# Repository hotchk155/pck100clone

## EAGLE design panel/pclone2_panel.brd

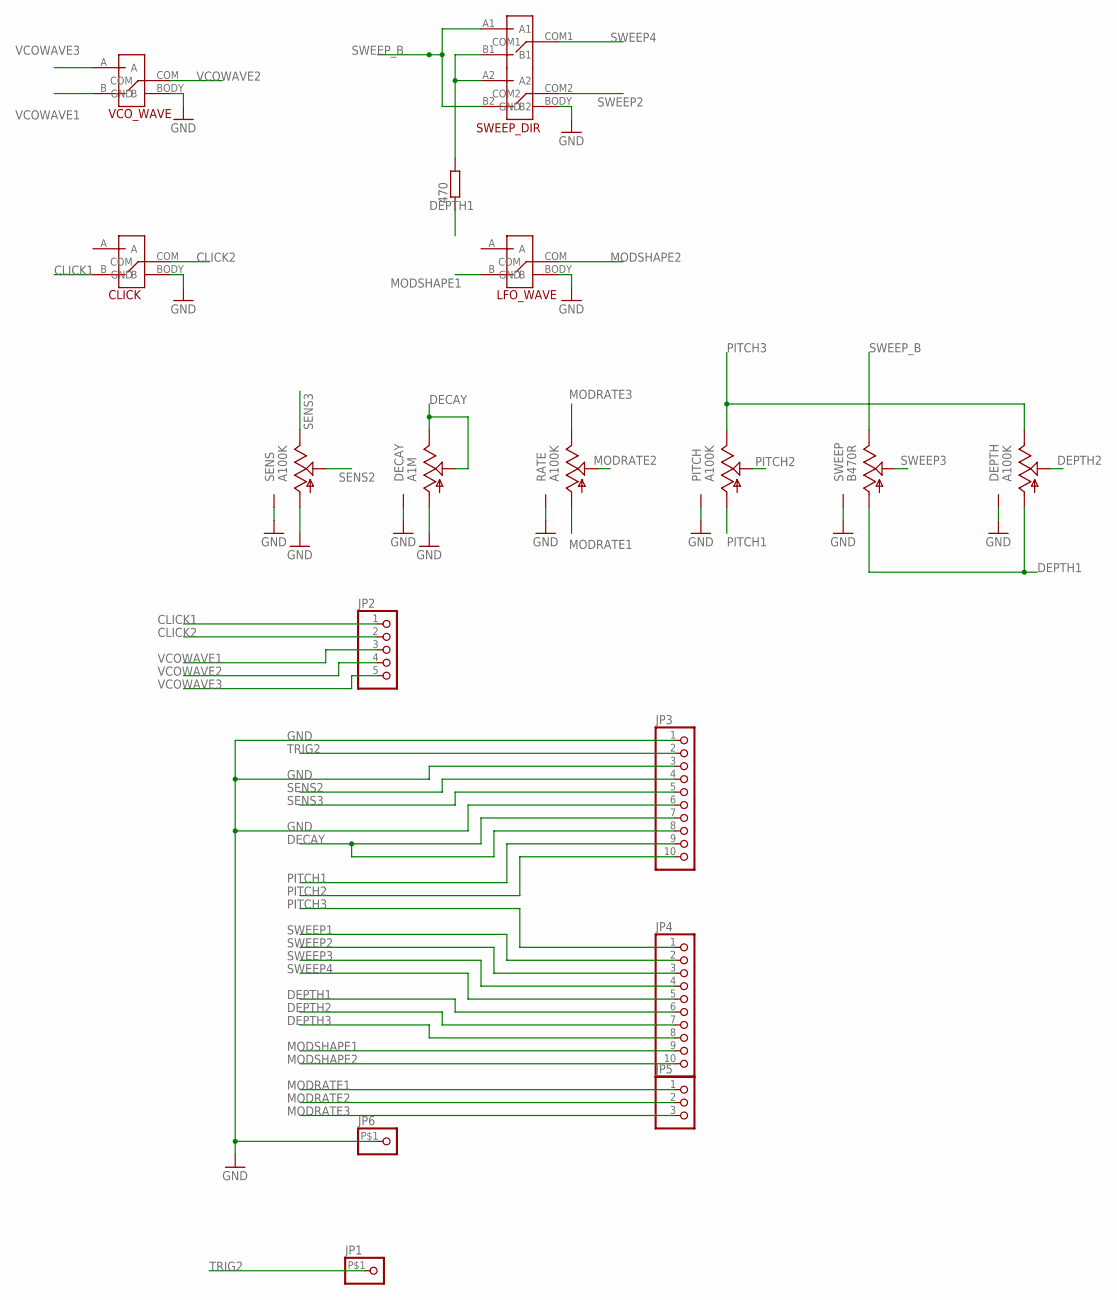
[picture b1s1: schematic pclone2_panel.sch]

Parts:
470: R-EU_R0805; R0805
CLICK: SPD_SMTD; SPDT_SMTD
DECAY: A1M; 16MM_POT_SMTD
DEPTH: A100K; 16MM_POT_SMTD
JP1, JP6: PINHD-1X1SMT; PINHEADPAD
JP2: HEADER-1X5SMT; 1X05_SMT
JP3, JP4: HEADER-1X10SMT; 1X10_SMT
JP5: HEADER-1X3SMT; 1X03_SMT
LFO_WAVE: SPD_SMTD; SPDT_SMTD
PITCH: A100K; 16MM_POT_SMTD
RATE: A100K; 16MM_POT_SMTD
SENS: A100K; 16MM_POT_SMTD
SWEEP: B470R; 16MM_POT_SMTD
SWEEP_DIR: DPDT_SMTD
VCO_WAVE: SPD_SMTD; SPDT_SMTD

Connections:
CLICK1: CLICK.B, JP2.1
CLICK2: CLICK.COM, JP2.2
DECAY: DECAY.B, DECAY.W, JP3.7, JP3.8
DEPTH1: 470.1, DEPTH.A, JP4.6, SWEEP.A
DEPTH2: DEPTH.W, JP4.7
DEPTH3: JP4.8
GND: CLICK.BODY (GND), DECAY.A, DECAY.BODY (GND), DEPTH.BODY (GND), JP3.1, JP3.3, JP3.6, JP6.P$1, LFO_WAVE.BODY (GND), PITCH.BODY (GND), RATE.BODY (GND), SENS.A, SENS.BODY (GND), SWEEP.BODY (GND), SWEEP_DIR.BODY (GND), VCO_WAVE.BODY (GND)
MODRATE1: JP5.1, RATE.A
MODRATE2: JP5.2, RATE.W
MODRATE3: JP5.3, RATE.B
MODSHAPE1: JP4.9, LFO_WAVE.B
MODSHAPE2: JP4.10, LFO_WAVE.COM
unnamed: 470.2, SWEEP_DIR.A2, SWEEP_DIR.B1
PITCH1: JP3.9, PITCH.A
PITCH2: JP3.10, PITCH.W
PITCH3: DEPTH.B, JP4.1, PITCH.B
SENS2: JP3.4, SENS.W
SENS3: JP3.5, SENS.B
SWEEP1: JP4.2
SWEEP2: JP4.3, SWEEP_DIR.COM2
SWEEP3: JP4.4, SWEEP.W
SWEEP4: JP4.5, SWEEP_DIR.COM1
SWEEP_B: SWEEP.B, SWEEP_DIR.A1, SWEEP_DIR.B2
TRIG2: JP1.P$1, JP3.2
VCOWAVE1: JP2.3, VCO_WAVE.B
VCOWAVE2: JP2.4, VCO_WAVE.COM
VCOWAVE3: JP2.5, VCO_WAVE.A

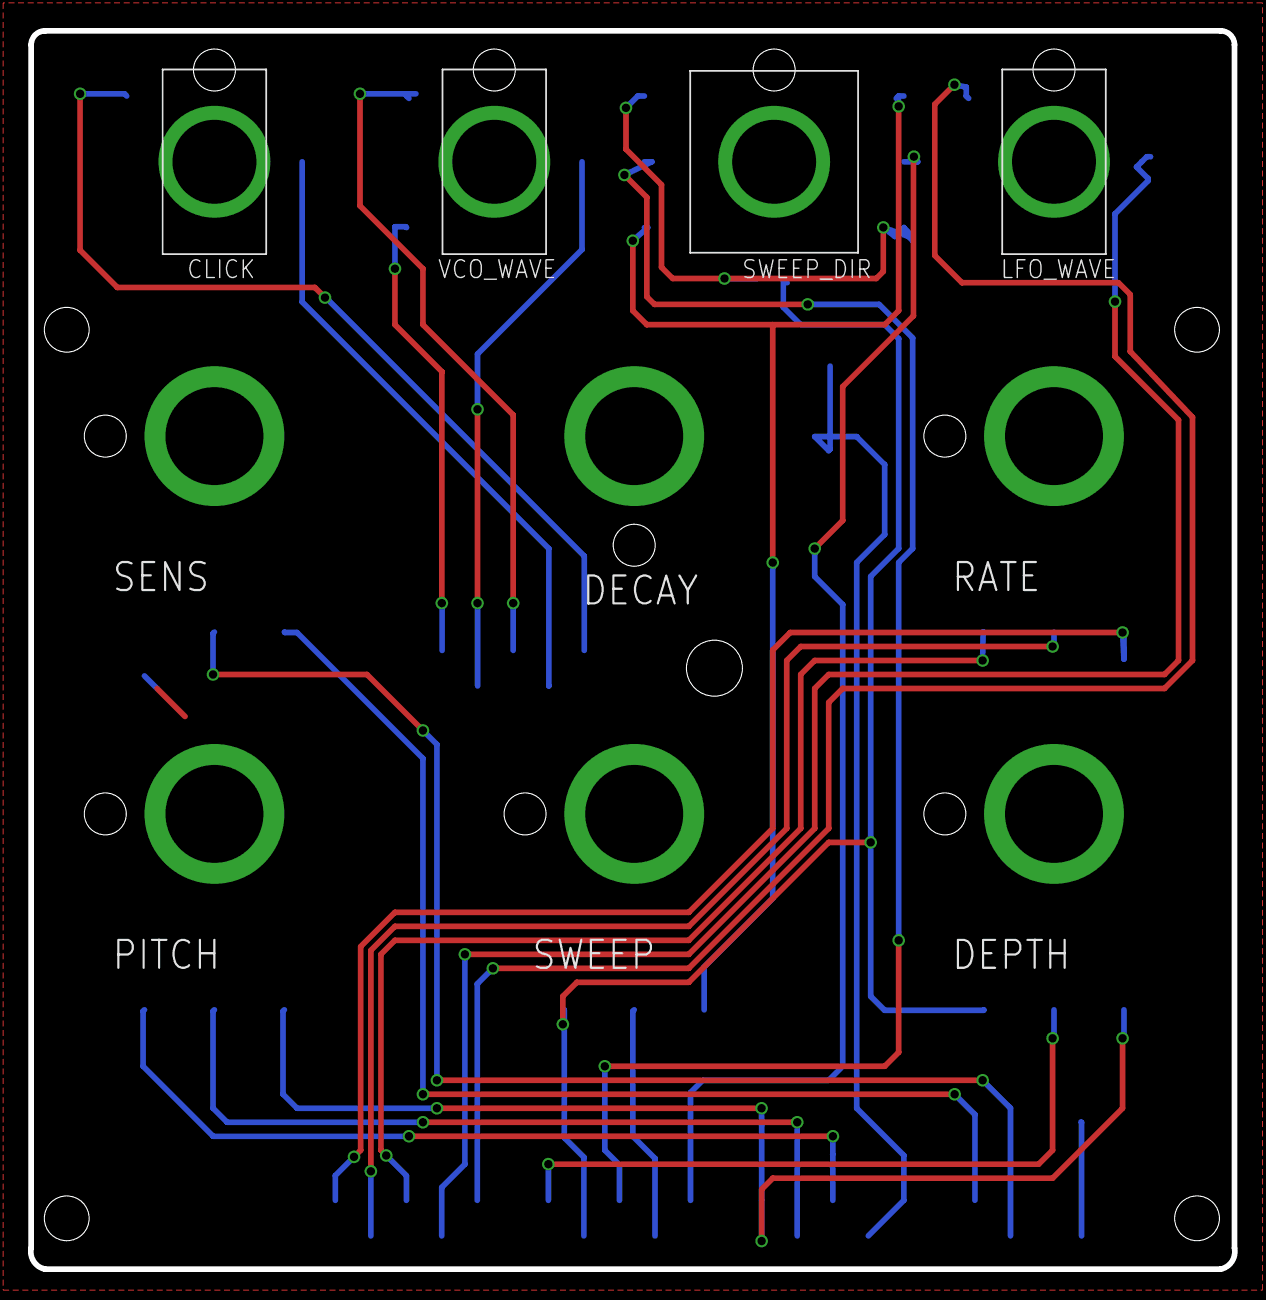
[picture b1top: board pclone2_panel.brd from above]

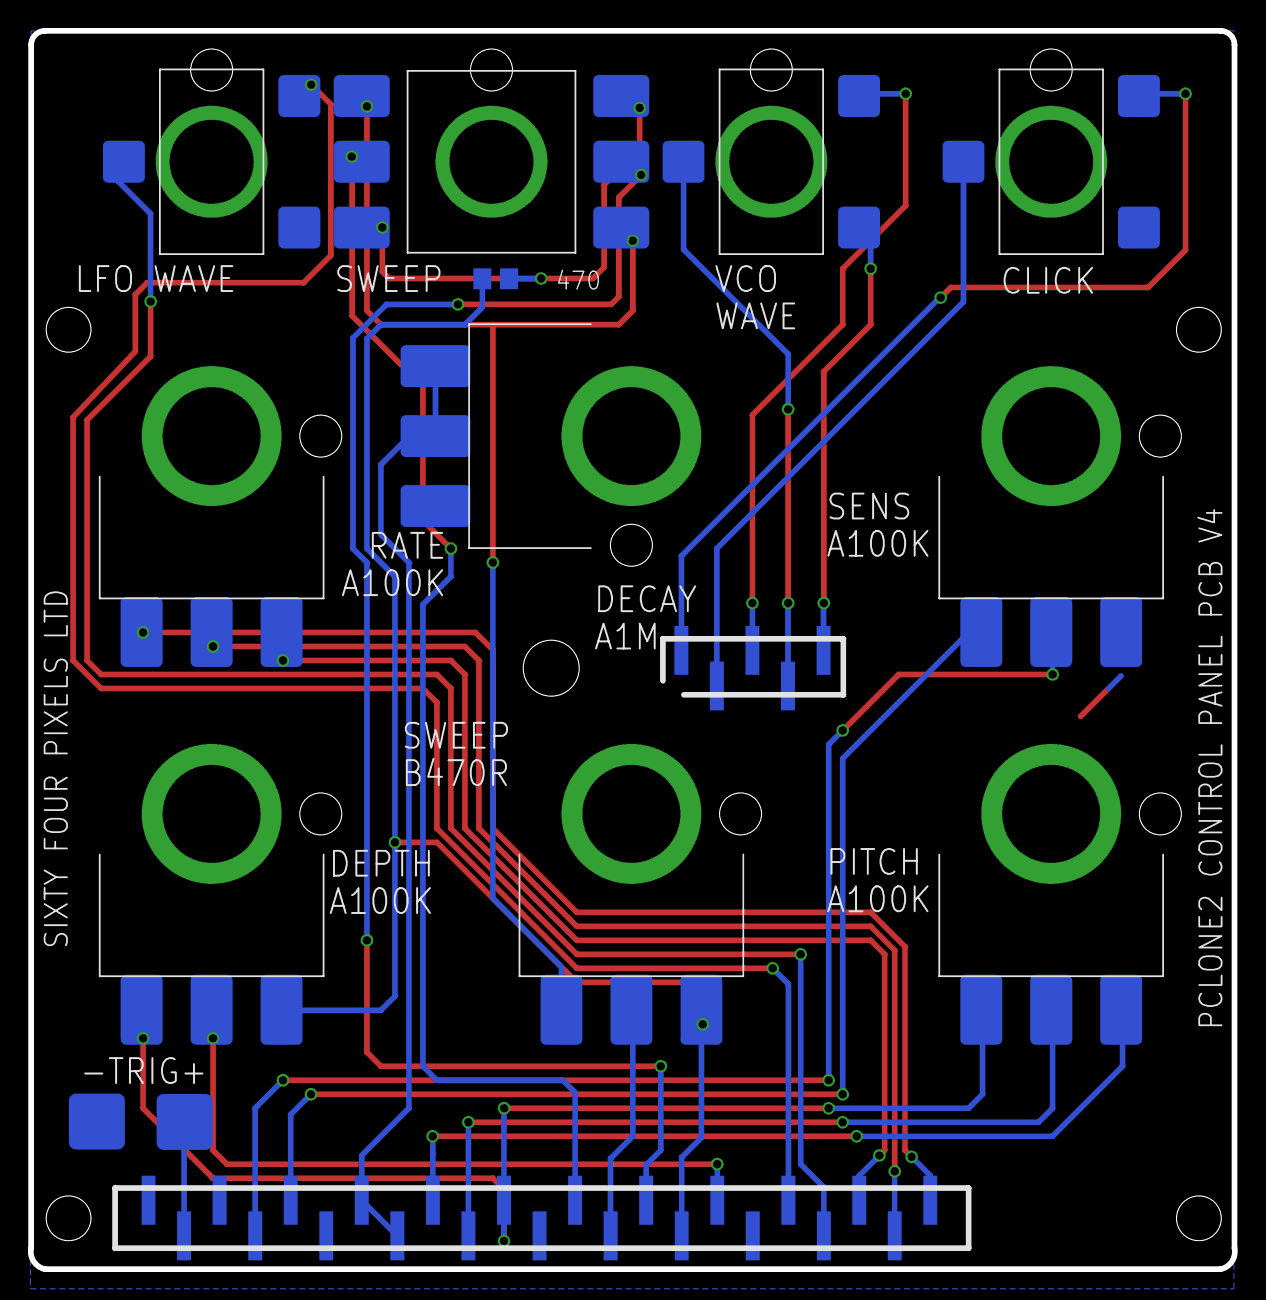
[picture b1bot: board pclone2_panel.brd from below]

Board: 2 copper layers, 86.0 x 88.5 mm, 17 parts (7 on the bottom side), 25 nets.

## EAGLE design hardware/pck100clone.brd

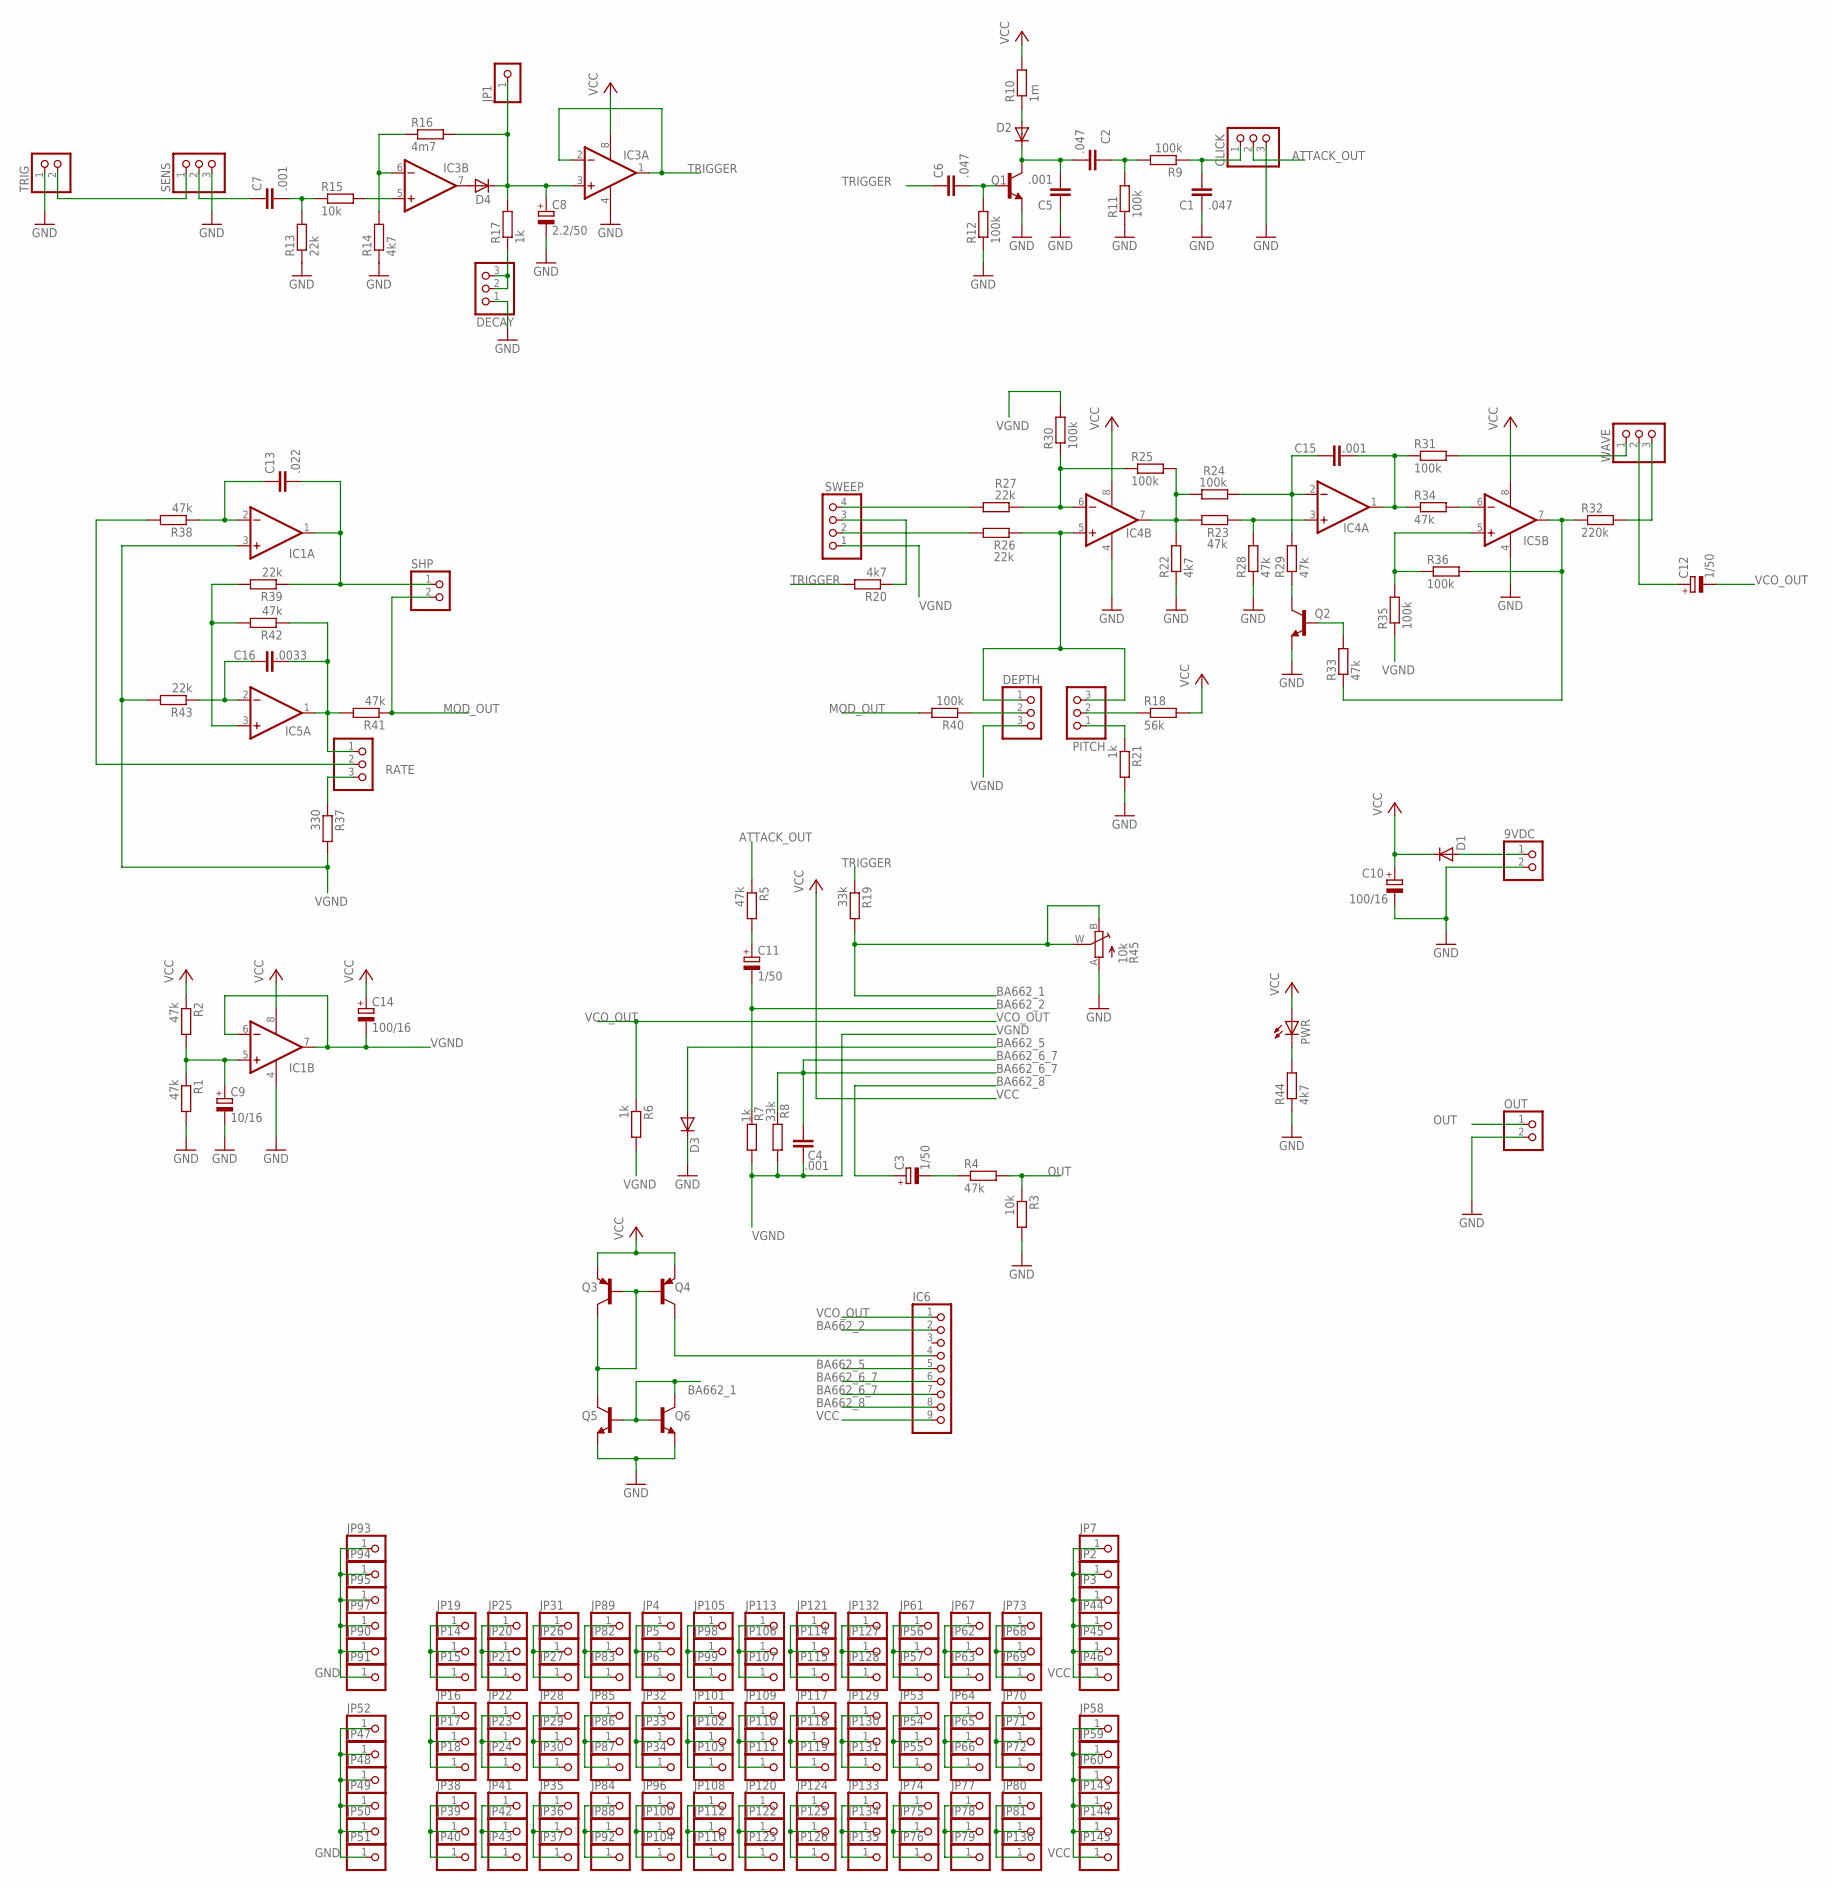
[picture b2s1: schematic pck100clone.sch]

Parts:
9VDC: PINHD-1X2; 1X02
C1, C2, C6: .047; C050-025X075
C3, C11, C12: 1/50; E2,5-5
C4, C5, C7, C15: .001; C050-025X075
C8: 2.2/50; E2,5-5
C9: 10/16; E2,5-5
C10, C14: 100/16; E2,5-5
C13: .022; C050-025X075
C16: .0033; C050-025X075
CLICK: PINHD-1X3; 1X03
D1: 1N4004; DO41-10
D2, D3, D4: 1N4148DO35-7; DO35-7
DECAY: PINHD-1X3; 1X03
DEPTH: PINHD-1X3; 1X03
IC1, IC3, IC4, IC5: LM358N; DIL08
IC6: PINHD-1X9; 1X09
JP1, JP2, JP3, JP4, JP5, JP6, JP7, JP14, JP15, JP16, JP17, JP18, JP19, JP20, JP21, JP22, JP23, JP24, JP25, JP26, JP27, JP28, JP29, JP30, JP31, JP32, JP33, JP34, JP35, JP36, JP37, JP38, JP39, JP40, JP41, JP42, JP43, JP44, JP45, JP46, JP47, JP48, JP49, JP50, JP51, JP52, JP53, JP54, JP55, JP56, JP57, JP58, JP59, JP60, JP61, JP62, JP63, JP64, JP65, JP66, JP67, JP68, JP69, JP70, JP71, JP72, JP73, JP74, JP75, JP76, JP77, JP78, JP79, JP80, JP81, JP82, JP83, JP84, JP85, JP86, JP87, JP88, JP89, JP90, JP91, JP92, JP93, JP94, JP95, JP96, JP97, JP98, JP99, JP100, JP101, JP102, JP103, JP104, JP105, JP106, JP107, JP108, JP109, JP110, JP111, JP112, JP113, JP114, JP115, JP116, JP117, JP118, JP119, JP120, JP121, JP122, JP123, JP124, JP125, JP126, JP127, JP128, JP129, JP130, JP131, JP132, JP133, JP134, JP135, JP136, JP143, JP144, JP145: PINHD-1X1; 1X01
OUT: PINHD-1X2; 1X02
PITCH: PINHD-1X3; 1X03
PWR: LED3MM
Q1, Q2: 2SC945; TO92-ECB
Q3, Q4: 2N3906; TO92
Q5, Q6: 2N3904; TO92
R1, R2, R4, R5, R23, R28, R29, R33, R34, R38, R41, R42: 47k; 0207/7
R3, R15: 10k; 0207/7
R6, R7, R17, R21: 1k; 0207/7
R8, R19: 33k; 0207/7
R9, R11, R12, R24, R25, R30, R31, R35, R36, R40: 100k; 0207/7
R10: 1m; 0207/7
R13, R26, R27, R39, R43: 22k; 0207/7
R14, R20, R22, R44: 4k7; 0207/7
R16: 4m7; 0207/7
R18: 56k; 0207/7
R32: 220k; 0207/7
R37: 330; 0207/7
R45: 10k; TRIM-N
RATE: PINHD-1X3; 1X03
SENS: PINHD-1X3; 1X03
SHP: PINHD-1X2; 1X02
SWEEP: PINHD-1X4; 1X04
TRIG: PINHD-1X2; 1X02
WAVE: PINHD-1X3; 1X03

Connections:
ATTACK_OUT: CLICK.2, R5.1
BA662_1: Q5.2 (B), Q6.1 (C), Q6.2 (B), R19.2, R45.B (E), R45.W (S)
BA662_2: C11.-, IC6.2, R7.1
BA662_5: D3.A, IC6.5
BA662_6_7: C4.2, IC6.6, IC6.7, R8.1
BA662_8: C3.+, IC6.8
GND: 9VDC.2, C1.1, C5.1, C8.-, C9.-, C10.-, CLICK.3, D3.C, DECAY.1, IC1.4 (V-), IC3.4 (V-), IC4.4 (V-), IC5.4 (V-), JP47.1, JP48.1, JP49.1, JP50.1, JP51.1, JP52.1, JP90.1, JP91.1, JP93.1, JP94.1, JP95.1, JP97.1, OUT.2, Q1.E, Q2.E, Q5.3 (E), Q6.3 (E), R1.2, R3.2, R11.1, R12.1, R13.1, R14.1, R21.2, R22.1, R28.1, R44.1, R45.A, SENS.3, TRIG.1
MOD_OUT: R40.2, R41.1, SHP.2
unnamed: SENS.1, TRIG.2
unnamed: 9VDC.1, D1.A
unnamed: C7.1, SENS.2
unnamed: C7.2, R13.2, R15.1
unnamed: IC3.5 (+IN), R15.2
unnamed: IC3.6 (-IN), R14.2, R16.1
unnamed: D4.A, IC3.7 (OUT)
unnamed: C8.+, D4.C, IC3.3 (+IN), JP1.1, R16.2, R17.2
unnamed: DECAY.2, DECAY.3, R17.1
unnamed: C6.2, Q1.B, R12.2
unnamed: C2.2, C5.2, D2.C, Q1.C
unnamed: D2.A, R10.1
unnamed: C2.1, R9.2, R11.2
unnamed: C1.2, CLICK.1, R9.1
unnamed: C13.2, IC1.1 (OUT), R39.1, SHP.1
unnamed: C13.1, IC1.2 (-IN), R38.1
unnamed: R38.2, RATE.2
unnamed: JP4.1, JP5.1, JP6.1
unnamed: C16.1, IC5.2 (-IN), R43.1
unnamed: C16.2, IC5.1 (OUT), R41.2, R42.1, RATE.1
unnamed: R20.1, SWEEP.3
unnamed: R37.1, RATE.3
unnamed: IC5.3 (+IN), R39.2, R42.2
unnamed: R27.2, SWEEP.4
unnamed: R26.2, SWEEP.2
unnamed: IC4.6 (-IN), R25.1, R27.1, R30.1
unnamed: DEPTH.1, IC4.5 (+IN), PITCH.3, R26.1
unnamed: DEPTH.2, R40.1
unnamed: PITCH.2, R18.1
unnamed: PITCH.1, R21.1
unnamed: C9.+, IC1.5 (+IN), R1.1, R2.2
unnamed: IC4.7 (OUT), R22.2, R23.1, R24.1, R25.2
unnamed: IC4.3 (+IN), R23.2, R28.2
unnamed: C15.2, IC4.2 (-IN), R24.2, R29.2
unnamed: Q2.C, R29.1
unnamed: Q2.B, R33.2
unnamed: C15.1, IC4.1 (OUT), R31.1, R34.1
unnamed: IC5.6 (-IN), R34.2
unnamed: R31.2, WAVE.1
unnamed: IC5.7 (OUT), R32.1, R33.1, R36.2
unnamed: R32.2, WAVE.3
unnamed: IC5.5 (+IN), R35.2, R36.1
unnamed: C12.+, WAVE.2
unnamed: PWR.K (C), R44.2
unnamed: IC6.4, Q4.1 (C)
unnamed: C11.+, R5.2
unnamed: Q3.1 (C), Q3.2 (B), Q4.2 (B), Q5.1 (C)
unnamed: JP14.1, JP15.1, JP19.1
unnamed: C3.-, R4.1
unnamed: JP16.1, JP17.1, JP18.1
unnamed: JP20.1, JP21.1, JP25.1
unnamed: JP22.1, JP23.1, JP24.1
unnamed: JP26.1, JP27.1, JP31.1
unnamed: JP28.1, JP29.1, JP30.1
unnamed: JP32.1, JP33.1, JP34.1
unnamed: JP35.1, JP36.1, JP37.1
unnamed: JP38.1, JP39.1, JP40.1
unnamed: JP41.1, JP42.1, JP43.1
unnamed: JP53.1, JP54.1, JP55.1
unnamed: JP56.1, JP57.1, JP61.1
unnamed: JP62.1, JP63.1, JP67.1
unnamed: JP64.1, JP65.1, JP66.1
unnamed: JP68.1, JP69.1, JP73.1
unnamed: JP70.1, JP71.1, JP72.1
unnamed: JP74.1, JP75.1, JP76.1
unnamed: JP77.1, JP78.1, JP79.1
unnamed: JP80.1, JP81.1, JP136.1
unnamed: JP98.1, JP99.1, JP105.1
unnamed: JP82.1, JP83.1, JP89.1
unnamed: JP85.1, JP86.1, JP87.1
unnamed: JP101.1, JP102.1, JP103.1
unnamed: JP106.1, JP107.1, JP113.1
unnamed: JP109.1, JP110.1, JP111.1
unnamed: JP114.1, JP115.1, JP121.1
unnamed: JP117.1, JP118.1, JP119.1
unnamed: JP84.1, JP88.1, JP92.1
unnamed: JP96.1, JP100.1, JP104.1
unnamed: JP108.1, JP112.1, JP116.1
unnamed: JP120.1, JP122.1, JP123.1
unnamed: JP124.1, JP125.1, JP126.1
unnamed: JP127.1, JP128.1, JP132.1
unnamed: JP129.1, JP130.1, JP131.1
unnamed: JP133.1, JP134.1, JP135.1
OUT: OUT.1, R3.1, R4.2
TRIGGER: C6.1, IC3.1 (OUT), IC3.2 (-IN), R19.1, R20.2
VCC: C10.+, C14.+, D1.C, IC1.8 (V+), IC3.8 (V+), IC4.8 (V+), IC5.8 (V+), IC6.9, JP2.1, JP3.1, JP7.1, JP44.1, JP45.1, JP46.1, JP58.1, JP59.1, JP60.1, JP143.1, JP144.1, JP145.1, PWR.A, Q3.3 (E), Q4.3 (E), R2.1, R10.2, R18.2
VCO_OUT: C12.-, IC6.1, R6.1
VGND: C4.1, C14.-, DEPTH.3, IC1.3 (+IN), IC1.6 (-IN), IC1.7 (OUT), R6.2, R7.2, R8.2, R30.2, R35.1, R37.2, R43.2, SWEEP.1

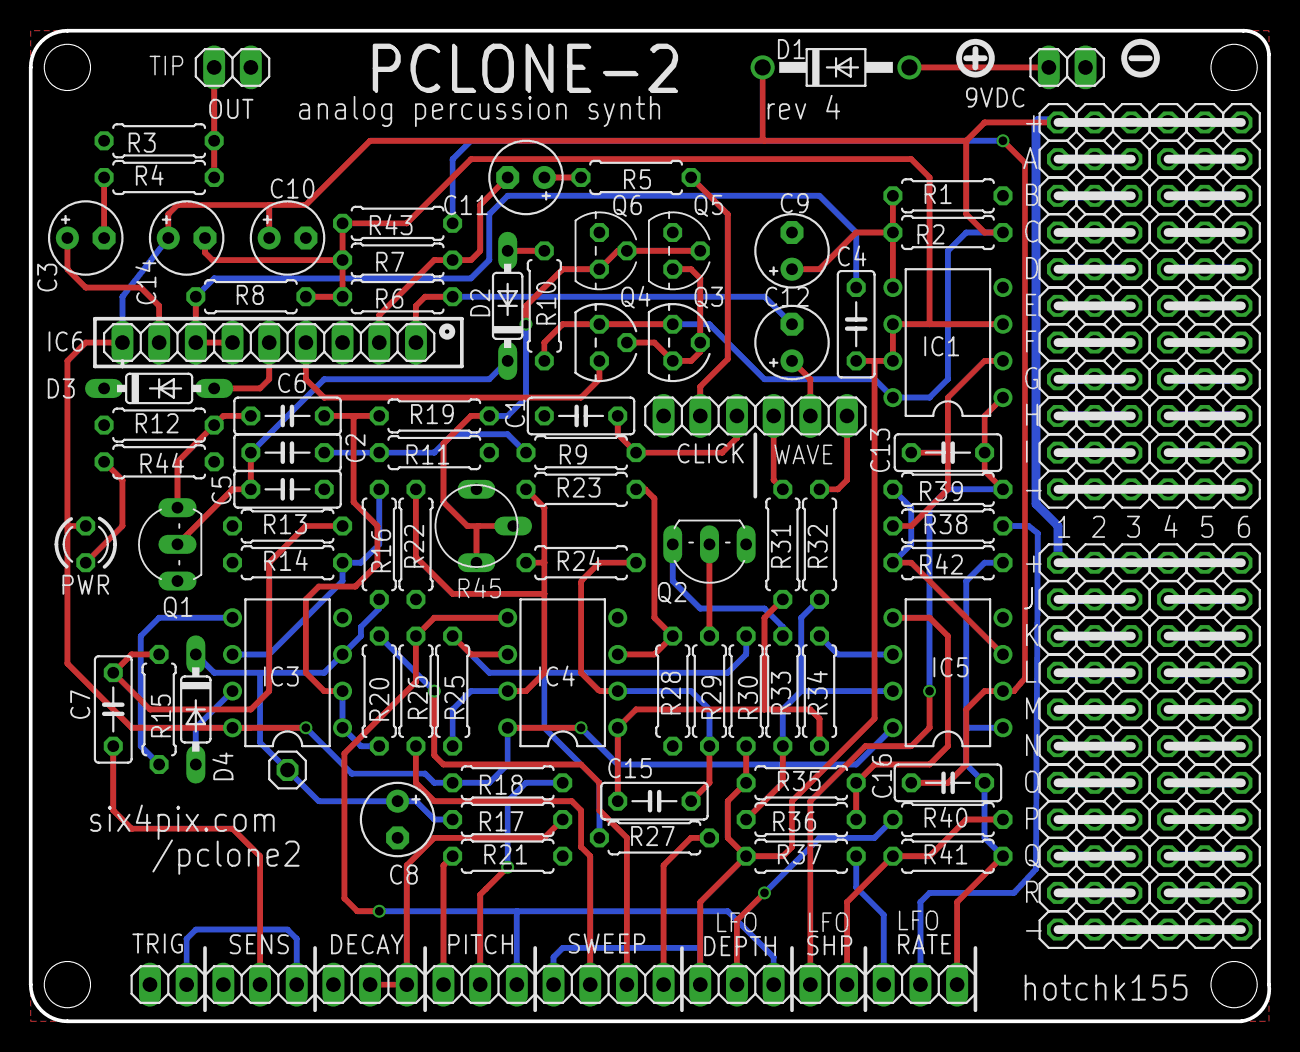
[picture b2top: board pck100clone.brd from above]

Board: 2 copper layers, 85.7 x 68.6 mm, 222 parts (0 on the bottom side), 96 nets.

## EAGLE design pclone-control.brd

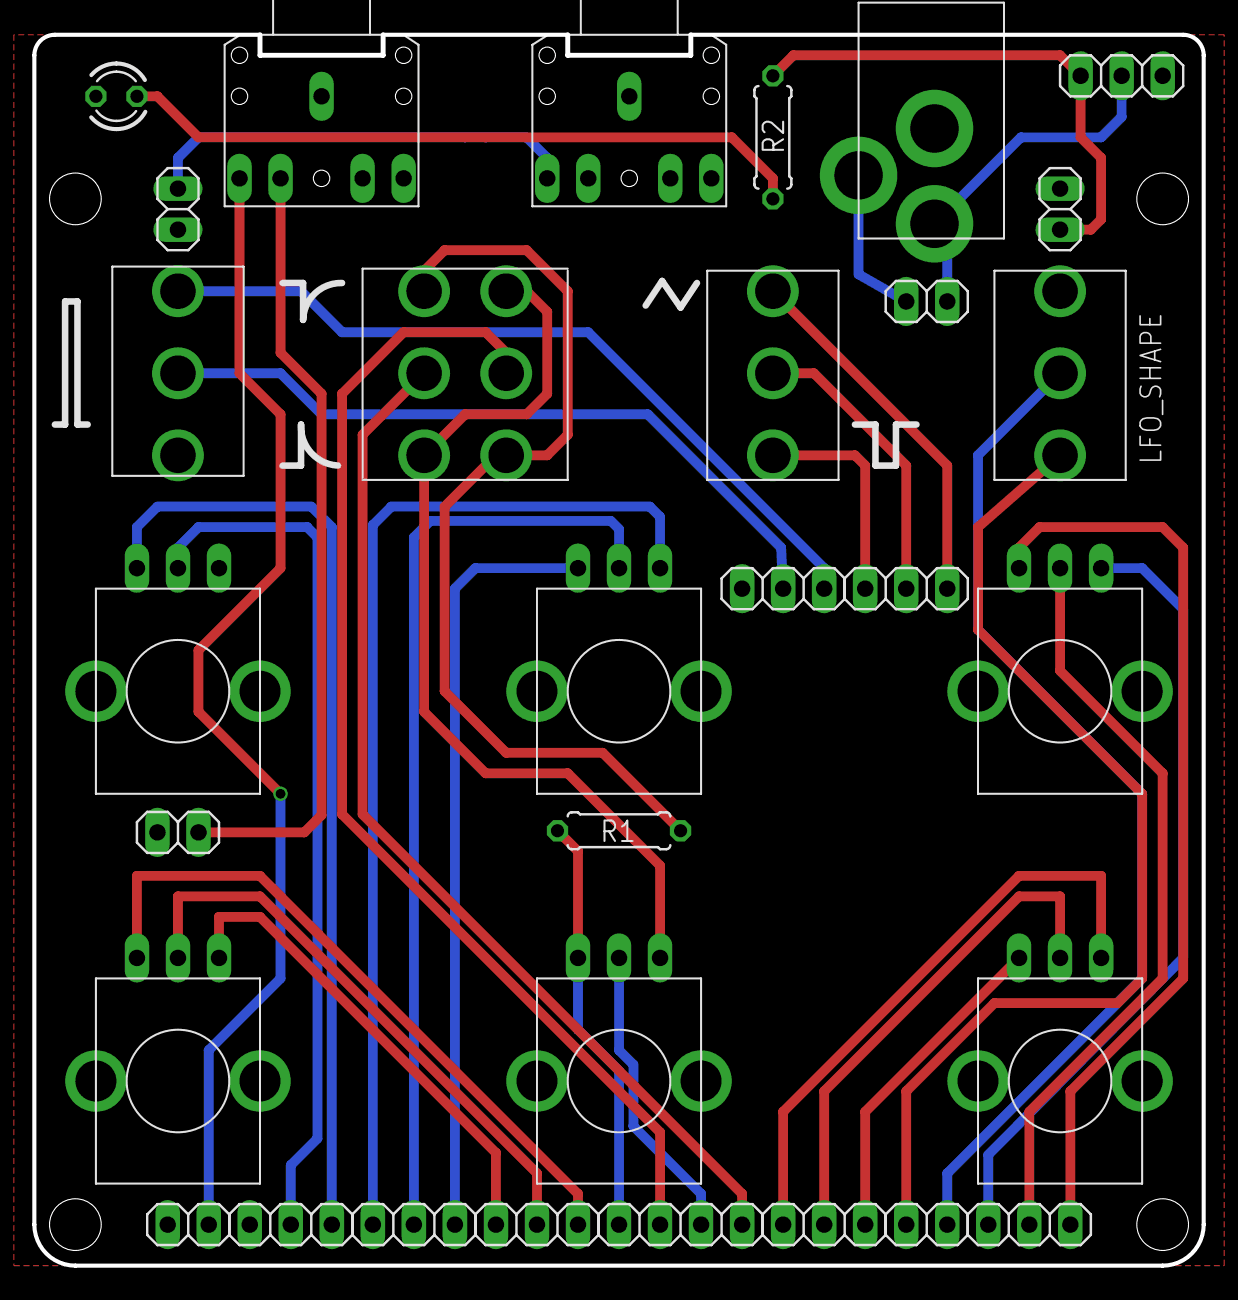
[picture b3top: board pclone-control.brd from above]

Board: 2 copper layers, 72.4 x 76.2 mm, 31 parts (0 on the bottom side), 35 nets.

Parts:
9VDC: 1X02
BATT: 1X02
CLICK: SPDT_SW
DECAY: ALPS_POT_SMALL; SMALL_ALPS_POT
DIR: DPDT_SW
IN: 1X02
INPUT: TRUCONNECTJACK
J1, J2, J3, J5, J7, J8, J9: 1X03
J4: 1X04
J6: 1X02
LED1: LED3MM
LFO_RATE: ALPS_POT_SMALL; SMALL_ALPS_POT
LFO_SHAPE: SPDT_SW
MOD: ALPS_POT_SMALL; SMALL_ALPS_POT
ONOFF: 1X03
OUT: 1X02
OUTPUT: TRUCONNECTJACK
PIEZO: 1X02
PITCH: ALPS_POT_SMALL; SMALL_ALPS_POT
R1: 500R; 0207/7
R2: 4k7; 0207/7
SENS: ALPS_POT_SMALL; SMALL_ALPS_POT
SWP: ALPS_POT_SMALL; SMALL_ALPS_POT
U$4: 2.1MMJACKTHM; PJ-102A
WAVE: SPDT_SW

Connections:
GND: 9VDC.2, IN.1, INPUT.RING, INPUT.RING_NC, INPUT.SLEEVE, J1.1, LED1.K, OUT.1, OUTPUT.RING, OUTPUT.RING_NC, OUTPUT.SLEEVE, PIEZO.1, SENS.A, U$4.RING
unnamed: J4.1, R1.2, SWP.B
unnamed: DIR.A1, DIR.B2, R1.1
unnamed: DIR.A2, DIR.B1, SWP.A
unnamed: DIR.COM1, J4.4
unnamed: DIR.COM2, J4.2
unnamed: J4.3, SWP.W
unnamed: J9.1, WAVE.B1
unnamed: J9.3, WAVE.A1
unnamed: J9.2, WAVE.COM1
unnamed: CLICK.B1, J8.1
unnamed: CLICK.COM1, J8.2
unnamed: J6.1, LFO_SHAPE.B1
unnamed: J6.2, LFO_SHAPE.COM1
unnamed: J1.2, SENS.W
unnamed: BATT.1, ONOFF.2, U$4.TIP
unnamed: J1.3, SENS.B
unnamed: DECAY.W, J2.2
unnamed: DECAY.A, J2.1
unnamed: DECAY.B, J2.3
unnamed: J5.2, MOD.W
unnamed: J5.1, MOD.A
unnamed: J5.3, MOD.B
unnamed: J3.2, PITCH.W
unnamed: J3.1, PITCH.A
unnamed: J3.3, PITCH.B
unnamed: J7.2, LFO_RATE.W
unnamed: J7.3, LFO_RATE.B
unnamed: J7.1, LFO_RATE.A
unnamed: BATT.2, U$4.RING_SW
unnamed: 9VDC.1, ONOFF.3, R2.1
unnamed: LED1.A, R2.2
unnamed: OUT.2, OUTPUT.TIP
unnamed: INPUT.TIP_NC, PIEZO.2
unnamed: IN.2, INPUT.TIP

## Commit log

2015-11-08 :space_invader: Added .gitattributes & .gitignore files
2015-11-08 fixes
2015-11-08 more changes
2015-11-08 stuff
2015-11-08 almost done?
2015-11-08 gitignore
2015-11-08 more fussing
2015-11-08 nggg
2015-11-25 tweaks
2015-11-26 pcb rev1
2015-12-26 added VCA pulldown
2015-12-26 remove VCA pin 3 connection to VGND
2015-12-26 moar stuff
2015-12-26 cv patch point
2015-12-26 control panel
2016-01-05 work in progress
2016-02-12 rev2
2016-06-13 rev3
2016-06-13 rev3forreal
2016-06-13 tidy up project
2016-07-11 REV4
    add vca input trim / add series polarity diode
2016-07-22 setup for cut
2016-09-08 docs
2017-01-15 typo
2018-11-24 control panel board
2018-11-24 PANEL CHANGES
2018-11-26 asas
2018-11-26 dsfdfs
2018-11-26 sdsds
2018-11-26 FIRST PCB FAB V1
2018-12-21 v2 - smt headers
2018-12-21 silk changes
2019-01-30 V3 reroute to avoid washers
2019-01-30 text moved
2019-02-26 change for new front panel pcb
2019-02-28 power socket change
2019-02-28 tweak
2019-04-18 New build instructions
2019-05-28 add mods doc
2019-11-20 add 4 colour band resistor codes
2019-11-20 oops
2020-05-12 V4 Panel
    Moved tracks away from hole. Added extra hole for piezo wires. Additional ground plane clearance
2021-11-18 bom.doc
2021-11-24 Update to build instructions for new front panel
